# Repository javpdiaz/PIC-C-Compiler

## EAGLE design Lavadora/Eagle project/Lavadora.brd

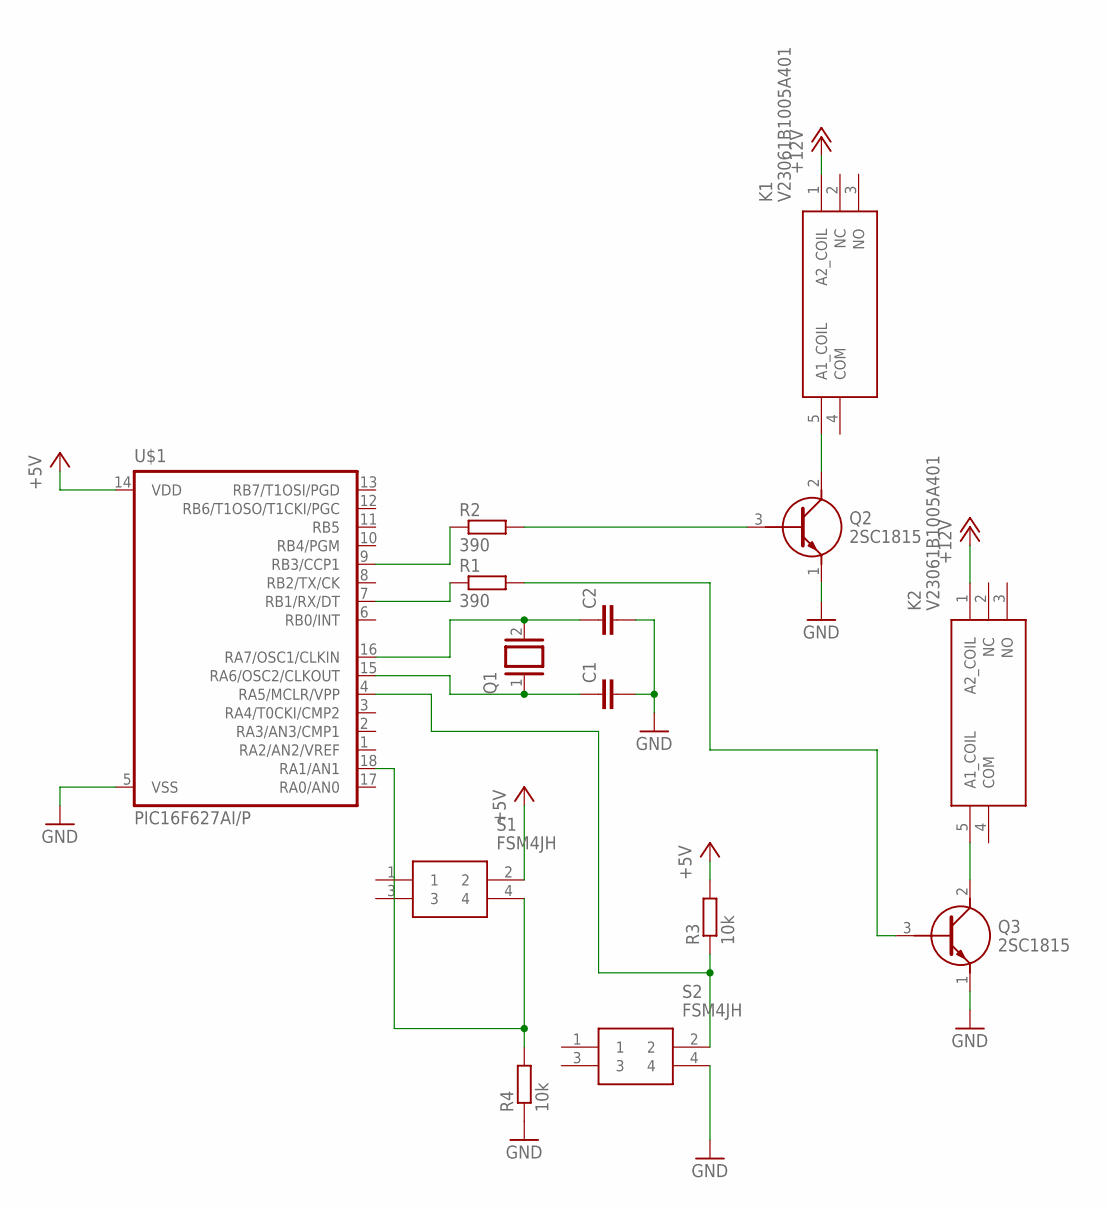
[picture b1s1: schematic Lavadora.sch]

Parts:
C1, C2: C-EU025-025X050; C025-025X050
K1, K2: V23061B1005A401
Q1: XTAL; Q
Q2, Q3: 2SC1815; CS_TO-92
R1, R2: 390; 0207/10
R3, R4: 10k; 0207/10
S1, S2: FSM4JH
U$1: PIC16F627AI/P; DIL18

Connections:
+5V: R3.2, S1.2, U$1.14 (VDD)
+12V: K1.1 (A2_COIL), K2.1 (A2_COIL)
GND: C1.2, C2.2, Q2.1 (E), Q3.1 (E), R4.1, S2.4, U$1.5 (VSS)
unnamed: C1.1, Q1.1, U$1.15 (RA6/OSC2/CLKOUT)
unnamed: C2.1, Q1.2, U$1.16 (RA7/OSC1/CLKIN)
unnamed: R1.1, U$1.7 (RB1/RX/DT)
unnamed: R2.1, U$1.9 (RB3/CCP1)
unnamed: Q2.3 (B), R2.2
unnamed: K1.5 (A1_COIL), Q2.2 (C)
unnamed: K2.5 (A1_COIL), Q3.2 (C)
unnamed: Q3.3 (B), R1.2
unnamed: R3.1, S2.2, U$1.4 (RA5/MCLR/VPP)
unnamed: R4.2, S1.4, U$1.18 (RA1/AN1)

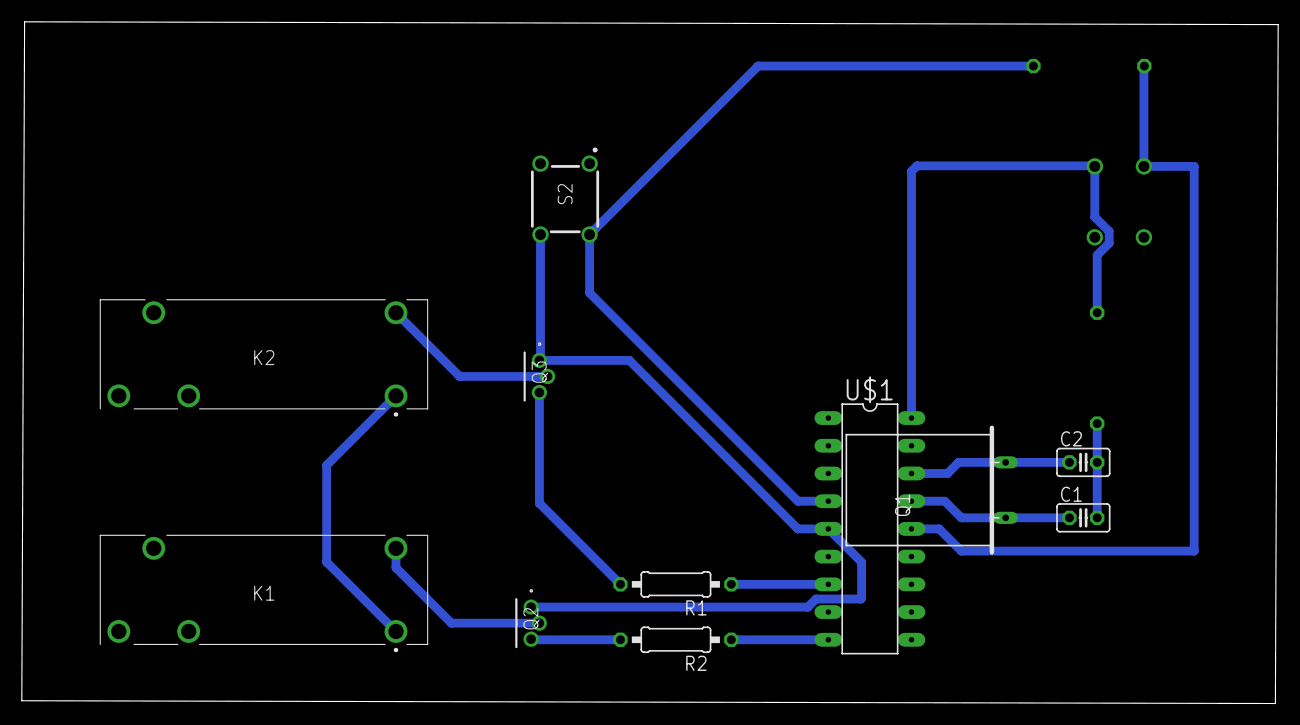
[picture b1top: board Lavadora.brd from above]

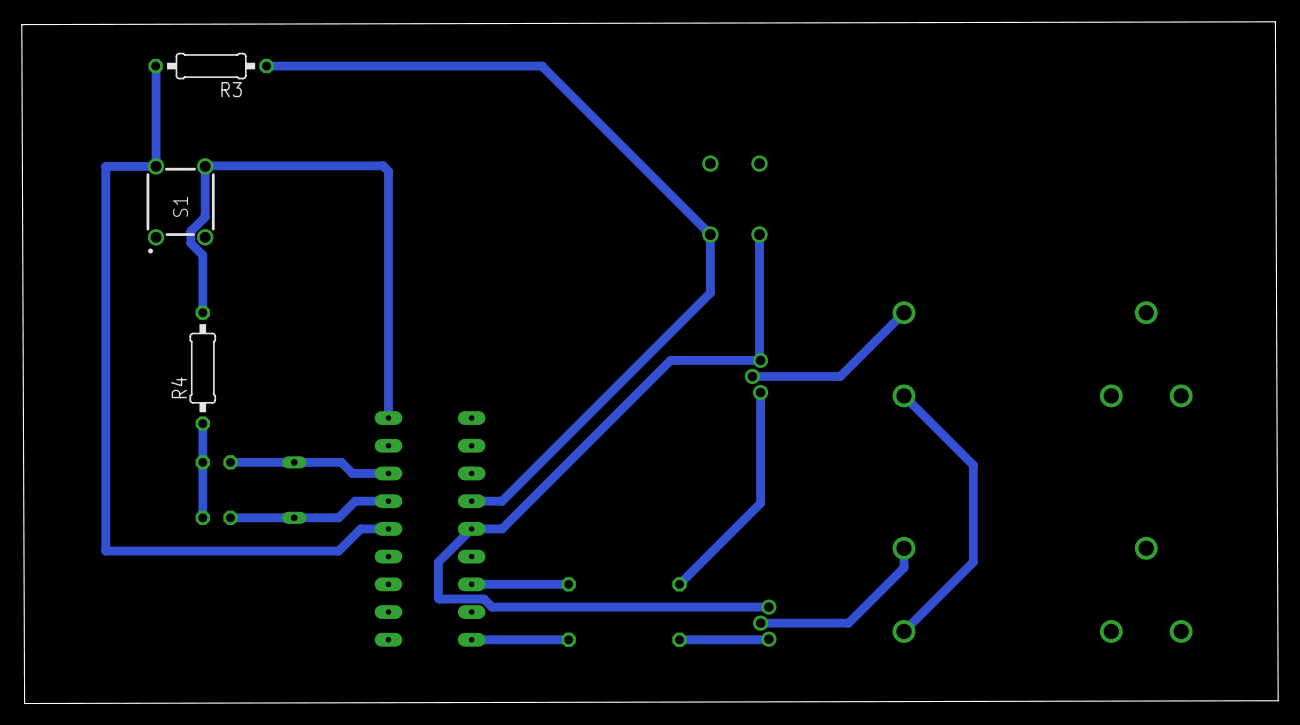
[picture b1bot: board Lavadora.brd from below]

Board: 2 copper layers, 115.1 x 62.5 mm, 14 parts (3 on the bottom side), 13 nets.

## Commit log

2022-01-04 prueba
2022-01-04 2022-01-03
2022-01-05 Cargador de bateria funcional
2022-02-06 hoy 2022-02-06
